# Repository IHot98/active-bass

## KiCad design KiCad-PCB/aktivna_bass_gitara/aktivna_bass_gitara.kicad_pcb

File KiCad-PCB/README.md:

# Aktivna bass gitara s ugrađenim zvučnikom

Dizajn tiskane pločice napravljem pomoću KiCad-a.

Tiskana pločica dizajnirana je kao jednoslojna pločica radi lakšeg procesa jetkanja, a komponente su dijelom THT i SMD jer u trenutku izrade nije bilo pristupa drugačijim.

## Slike

Prikaz dizajna pločice

3D Prikaz

3D Prikaz

Izrađeni sklop

Izrađeni sklop

Kompletirana bass gitara

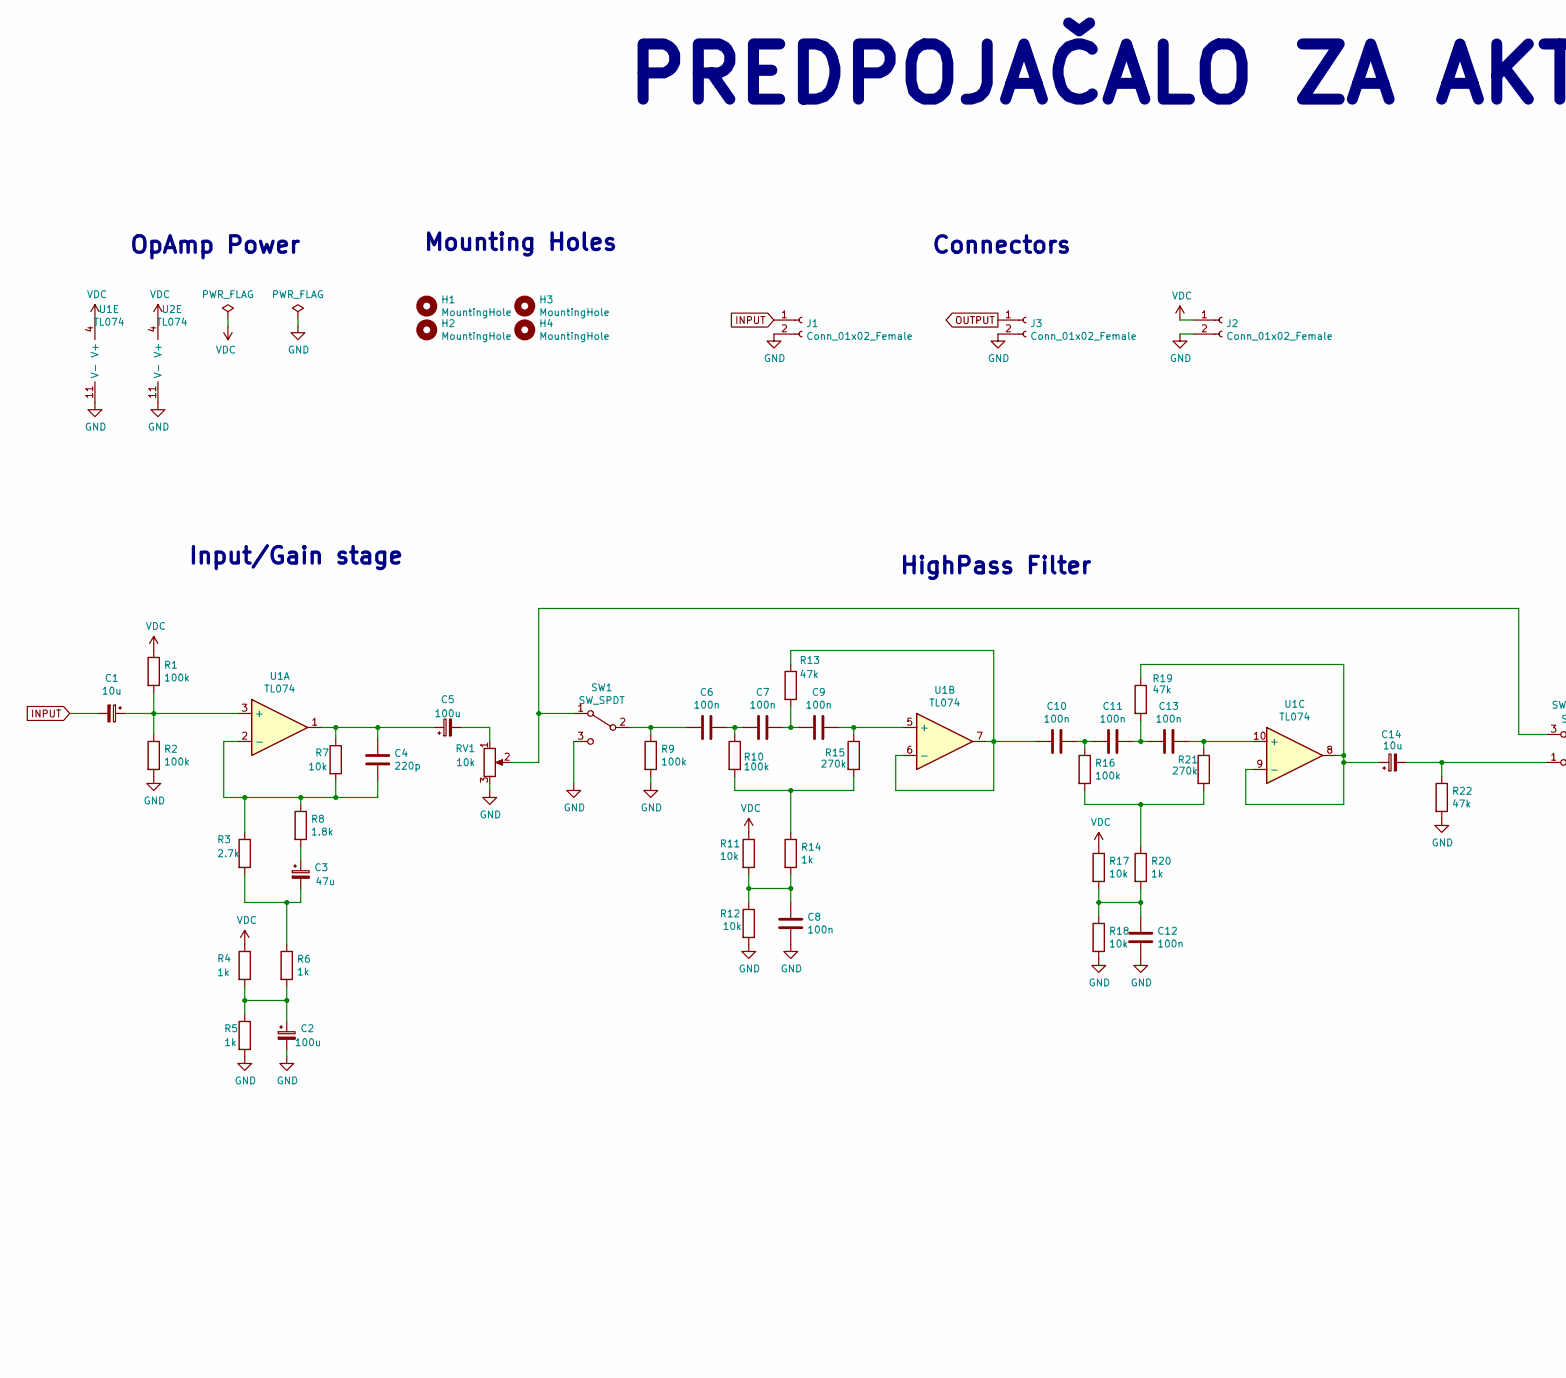
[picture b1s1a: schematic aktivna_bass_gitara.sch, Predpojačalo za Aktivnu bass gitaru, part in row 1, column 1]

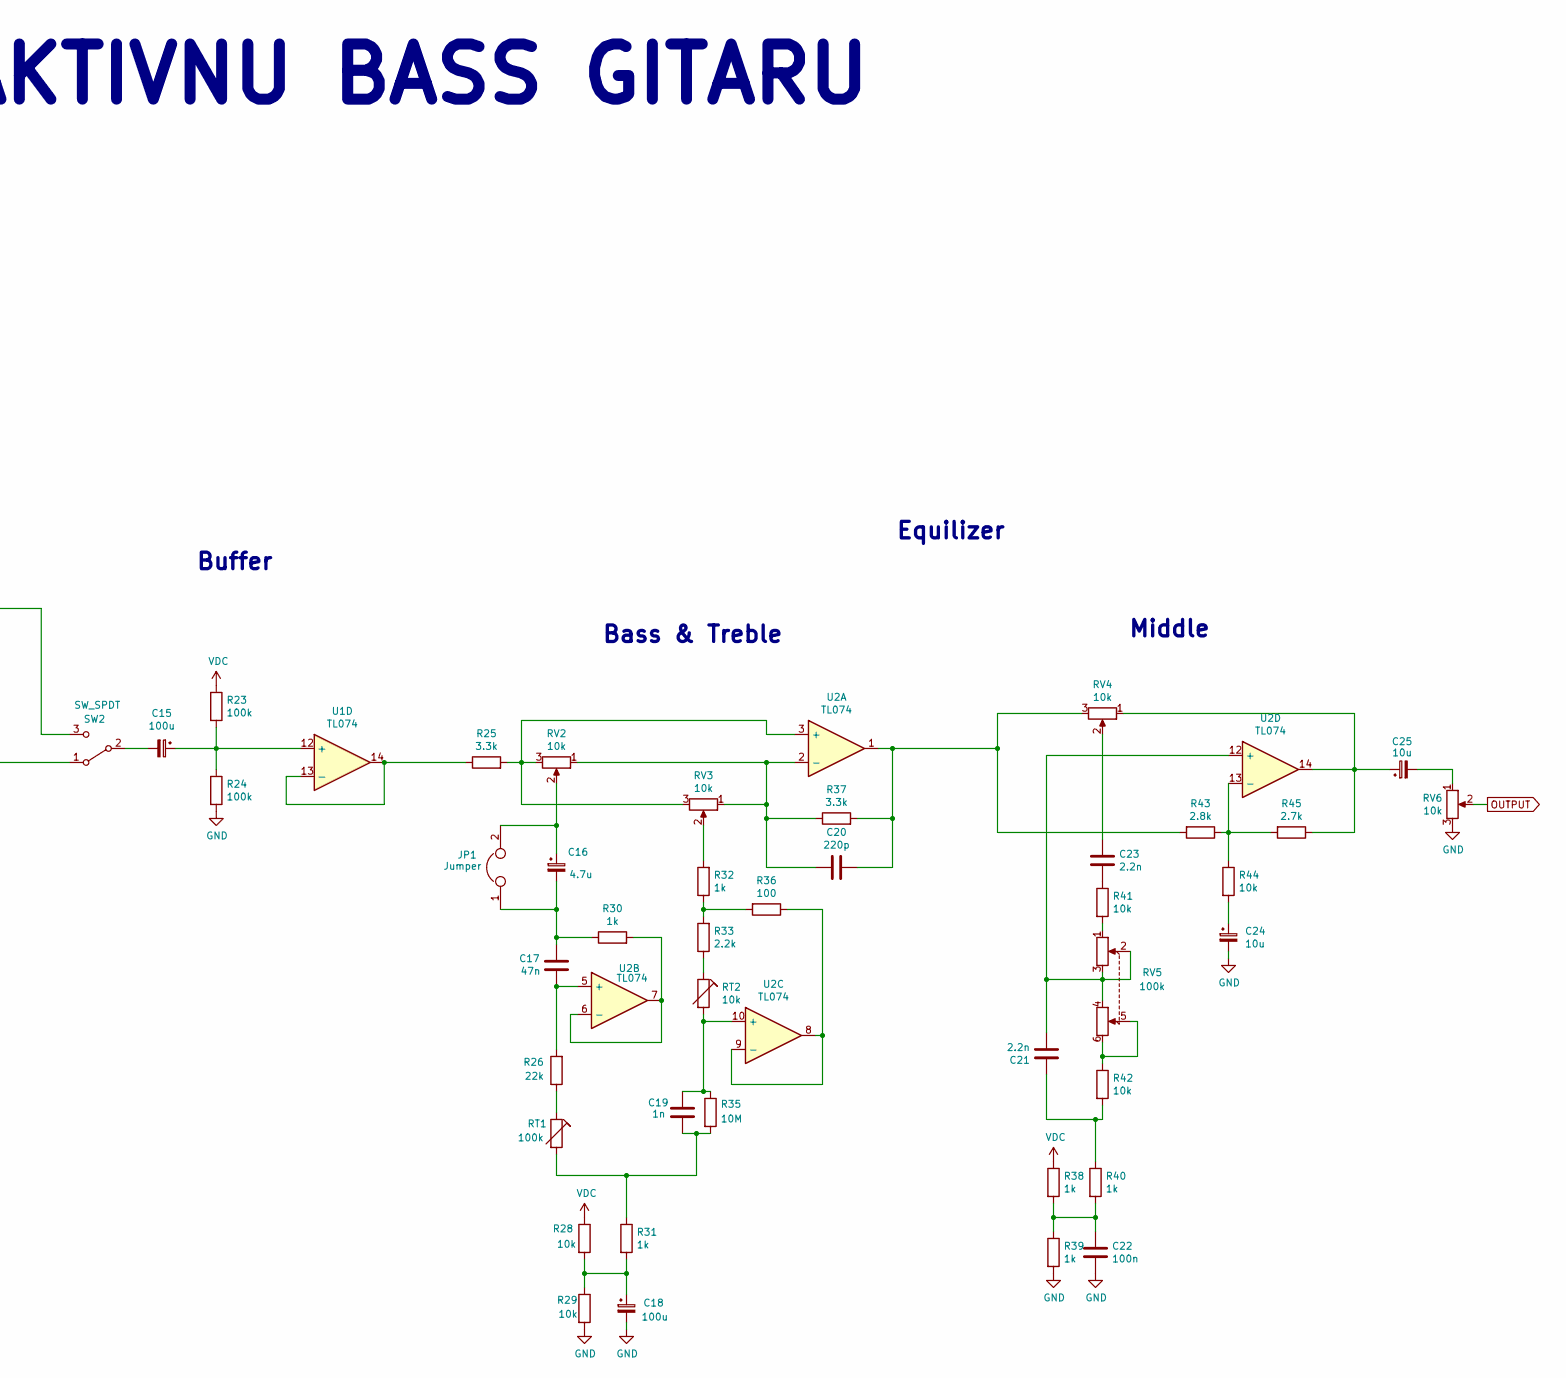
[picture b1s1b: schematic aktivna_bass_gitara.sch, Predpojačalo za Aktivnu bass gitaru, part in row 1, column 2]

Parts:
C1, C14, C24: 10u; CP_Radial_D5.0mm_P2.00mm
C2, C15, C18: 100u; CP_Radial_D6.3mm_P2.50mm
C3: 47u; CP_Radial_D5.0mm_P2.00mm
C4, C20: 220p; C_Disc_D3.0mm_W1.6mm_P2.50mm
C5: 100u; CP_Radial_D5.0mm_P2.00mm
C6, C7, C8, C9, C10, C11, C12, C13, C22: 100n; C_0805_2012Metric_Pad1.18x1.45mm_HandSolder
C16: 4.7u; CP_Radial_D5.0mm_P2.00mm
C17: 47n; C_0805_2012Metric_Pad1.18x1.45mm_HandSolder
C19: 1n; C_Rect_L7.0mm_W2.0mm_P5.00mm
C21, C23: 2.2n; CP_Radial_D5.0mm_P2.00mm
C25: 10u; CP_Radial_D8.0mm_P3.50mm
H1, H2, H3, H4: MountingHole; MountingHole_3.2mm_M3
J1, J2, J3: Conn_01x02_Female; PinHeader_1x02_P2.54mm_Vertical
JP1: Jumper; PinHeader_1x02_P2.54mm_Vertical
R1, R2, R9, R10, R16: 100k; R_0805_2012Metric_Pad1.20x1.40mm_HandSolder
R3, R45: 2.7k; R_0805_2012Metric_Pad1.20x1.40mm_HandSolder
R4, R5, R14, R30, R32, R39, R40: 1k; R_0805_2012Metric_Pad1.20x1.40mm_HandSolder
R6, R20, R31, R38: 1k; R_Axial_DIN0204_L3.6mm_D1.6mm_P5.08mm_Horizontal
R7, R11, R12, R17, R18, R28, R29, R41, R42, R44: 10k; R_0805_2012Metric_Pad1.20x1.40mm_HandSolder
R8: 1.8k; R_0805_2012Metric_Pad1.20x1.40mm_HandSolder
R13, R19: 47k; R_0805_2012Metric_Pad1.20x1.40mm_HandSolder
R15, R21: 270k; R_0805_2012Metric_Pad1.20x1.40mm_HandSolder
R22: 47k; R_Axial_DIN0204_L3.6mm_D1.6mm_P5.08mm_Horizontal
R23, R24: 100k; R_Axial_DIN0204_L3.6mm_D1.6mm_P5.08mm_Horizontal
R25: 3.3k; R_Axial_DIN0204_L3.6mm_D1.6mm_P5.08mm_Horizontal
R26: 22k; R_0805_2012Metric_Pad1.20x1.40mm_HandSolder
R33: 2.2k; R_Axial_DIN0204_L3.6mm_D1.6mm_P5.08mm_Horizontal
R35: 10M; R_0805_2012Metric_Pad1.20x1.40mm_HandSolder
R36: 100; R_Axial_DIN0204_L3.6mm_D1.6mm_P5.08mm_Horizontal
R37: 3.3k; R_0805_2012Metric_Pad1.20x1.40mm_HandSolder
R43: 2.8k; R_Axial_DIN0204_L3.6mm_D1.6mm_P5.08mm_Horizontal
RT1: 100k; R_Axial_DIN0204_L3.6mm_D1.6mm_P5.08mm_Horizontal
RT2: 10k; R_Axial_DIN0204_L3.6mm_D1.6mm_P5.08mm_Horizontal
RV1, RV2, RV3, RV4, RV6: 10k; PinHeader_1x03_P2.54mm_Vertical
RV5: 100k; PinHeader_2x03_P2.54mm_Vertical
SW1, SW2: SW_SPDT; PinHeader_1x03_P2.54mm_Vertical
U1, U2: TL074; SOIC-14_3.9x8.7mm_P1.27mm

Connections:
GND: C2.2, C8.1, C12.1, C18.2, C22.1, C24.2, J1.2, J2.2, J3.2, R2.2, R5.2, R9.2, R12.2, R18.2, R22.2, R24.2, R29.2, R39.2, RV1.3, RV6.3, SW1.3 (C), U1.11 (V-), U2.11 (V-)
INPUT: C1.2, J1.1
unnamed: C1.1, R1.2, R2.1, U1.3 (+)
unnamed: C2.1, R4.2, R5.1, R6.2
unnamed: C3.1, R8.2
unnamed: C3.2, R3.2, R6.1
unnamed: C4.1, R3.1, R7.2, R8.1, U1.2 (-)
unnamed: C4.2, C5.1, R7.1, U1.1
unnamed: C5.2, RV1.1
unnamed: C6.1, C7.2, R10.1
unnamed: C6.2, R9.1, SW1.2 (B)
unnamed: C7.1, C9.2, R13.2
unnamed: C8.2, R11.2, R12.1, R14.2
unnamed: C9.1, R15.1, U1.5 (+)
unnamed: C10.1, C11.2, R16.1
unnamed: C10.2, R13.1, U1.6 (-), U1.7
unnamed: C11.1, C13.2, R19.2
unnamed: C12.2, R17.2, R18.1, R20.2
unnamed: C13.1, R21.1, U1.10 (+)
unnamed: C14.1, R19.1, U1.8, U1.9 (-)
unnamed: C14.2, R22.1, SW2.1 (A)
unnamed: C15.1, R23.2, R24.1, U1.12 (+)
unnamed: C15.2, SW2.2 (B)
unnamed: C16.1, JP1.2, RV2.2
unnamed: C16.2, C17.2, JP1.1, R30.1
unnamed: C17.1, R26.2, U2.5 (+)
unnamed: C18.1, R28.2, R29.1, R31.2
unnamed: C19.1, R35.1, RT2.2, U2.10 (+)
unnamed: C19.2, R31.1, R35.2, RT1.2
unnamed: C20.1, R37.2, R43.2, RV4.3, U2.1
unnamed: C20.2, R37.1, RV2.1, RV3.1, U2.2 (-)
unnamed: C21.1, RV5.2, RV5.3, RV5.4, U2.12 (+)
unnamed: C21.2, R40.1, R42.2
unnamed: C22.2, R38.2, R39.1, R40.2
unnamed: C23.1, R41.1
unnamed: C23.2, RV4.2
unnamed: C24.1, R44.2
unnamed: C25.1, R45.1, RV4.1, U2.14
unnamed: C25.2, RV6.1
unnamed: R10.2, R14.1, R15.2
unnamed: R16.2, R20.1, R21.2
unnamed: R25.1, U1.13 (-), U1.14
unnamed: R25.2, RV2.3, RV3.3, U2.3 (+)
unnamed: R26.1, RT1.1
unnamed: R30.2, U2.6 (-), U2.7
unnamed: R32.1, R33.2, R36.2
unnamed: R32.2, RV3.2
unnamed: R33.1, RT2.1
unnamed: R36.1, U2.8, U2.9 (-)
unnamed: R41.2, RV5.1
unnamed: R42.1, RV5.5, RV5.6
unnamed: R43.1, R44.1, R45.2, U2.13 (-)
unnamed: RV1.2, SW1.1 (A), SW2.3 (C)
OUTPUT: J3.1, RV6.2
VDC: J2.1, R1.1, R4.1, R11.1, R17.1, R23.1, R28.1, R38.1, U1.4 (V+), U2.4 (V+)

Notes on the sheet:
OpAmp Power
Mounting Holes
Connectors
Input/Gain stage
HighPass Filter
Buffer
Bass & Treble
Middle
Equilizer
PREDPOJAČALO ZA AKTIVNU BASS GITARU

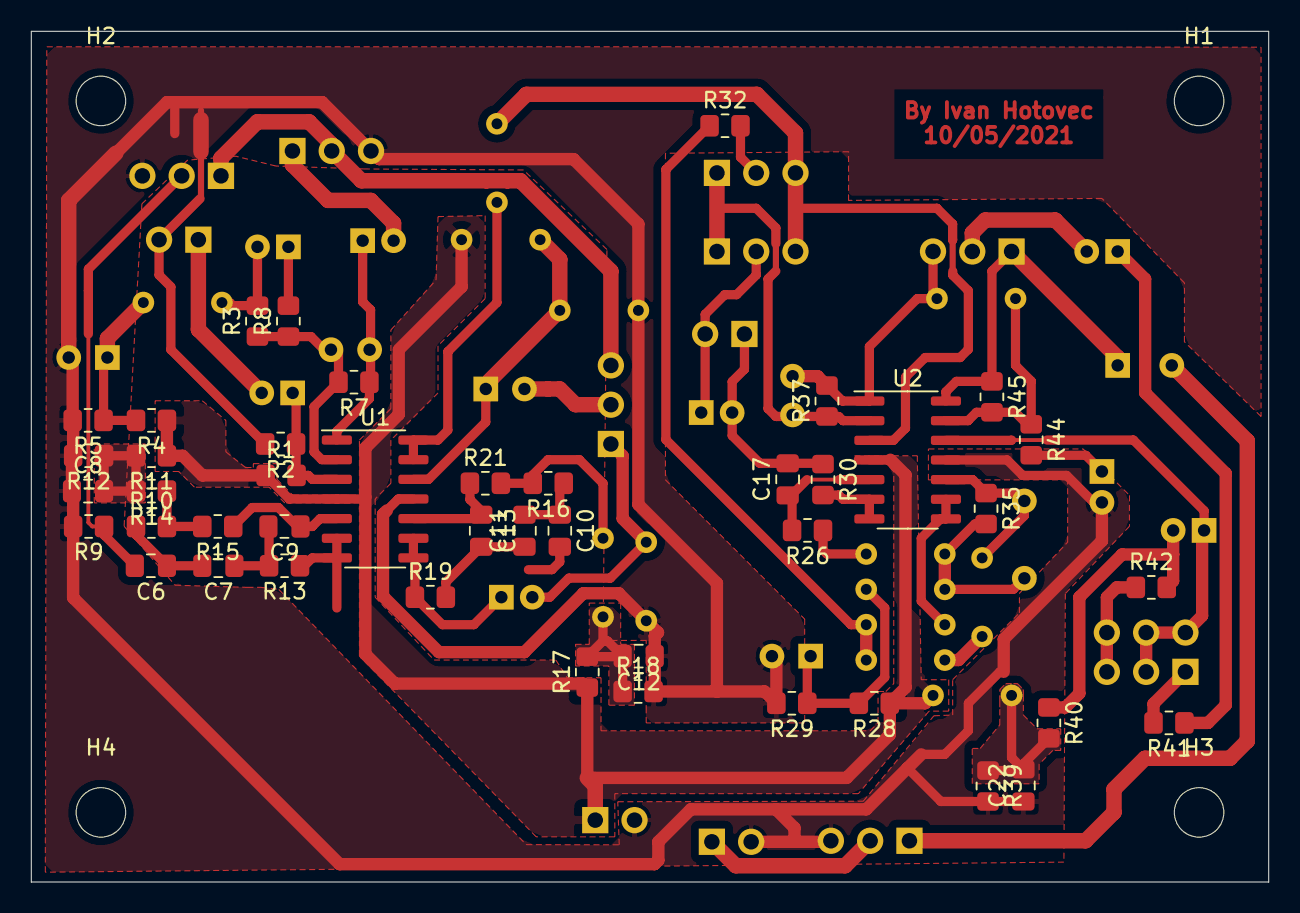
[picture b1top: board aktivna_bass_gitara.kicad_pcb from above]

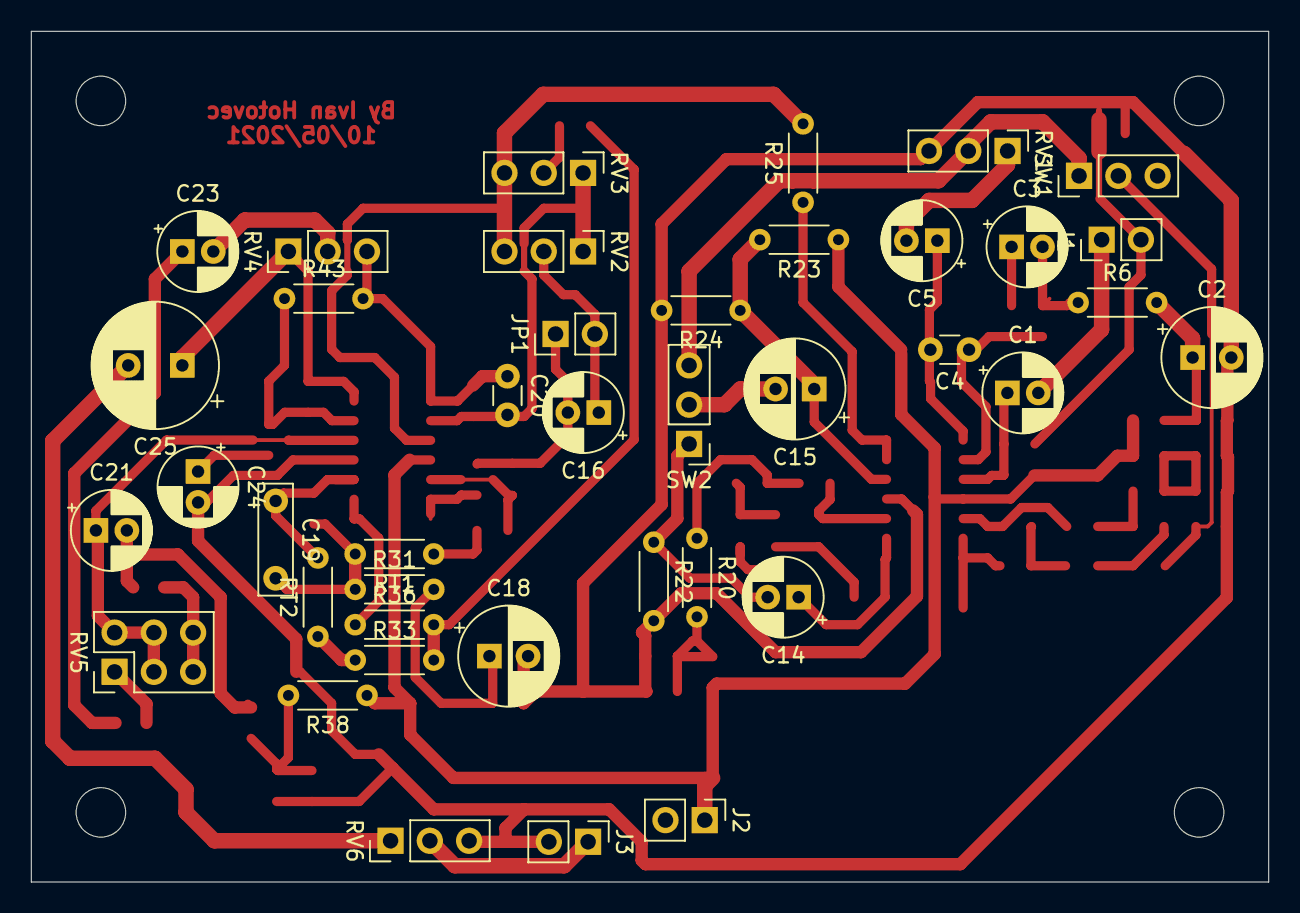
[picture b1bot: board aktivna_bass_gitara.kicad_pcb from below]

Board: 2 copper layers, 80.0 x 55.0 mm, 88 parts (40 on the bottom side), 55 nets.

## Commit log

2021-08-08 prvi
    prvi
2021-08-09 v2
    v2
2021-08-09 v3
    v3
